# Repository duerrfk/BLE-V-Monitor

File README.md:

BLE-V-Monitor is a battery voltage monitor for vehicles (cars, motorbikes). It consists of an Arduino-based monitoring device and an Android app. The BLE-V-Monitor device is connected to the car battery to monitor the battery voltage and record voltage histories. The app queries the current voltage and voltage history via Bluetooth Low Energy (BLE) and displays them to the user.

The main features of BLE-V-Monitor are:

- Current voltage and battery charge status monitoring
- Recording of minutely, hourly, and daily voltage histories
- Bluetooth Low Energy (BLE) to transmit voltage samples to smartphones, tablets, Internet gateways, etc.
- Very low energy consumption
- Android app for displaying current voltage and voltage histories
- Open source hardware (CERN Open Hardware Licence v1.2) and software (Apache License 2.0)

The following images show the BLE-V-Monitor device and screenshots from the app.

# Implementation

BLE-V-Monitor consists of two parts: 

* the BLE-V-Monitor device (PCB and Arduino software)
* a smartphone app for Android. 

You can find the following files here:

* Schematics and PCB layout (Eagle files) of the monitoring device: directory `eagle`.
* Arduino source code for monitor device: directory `src`.
* BLE service definition for nRF8001 used by monitoring device: directory `nRFgo_studio`. 
* Android app source code: directory `android`.

The BLE-V-Monitor device periodically samples the voltage of the battery, and the app uses Bluetooth Low Energy (BLE) to query the battery voltage when the smartphone is close to the car. Instead of using a smartphone, you could also implement a client for other devices, e.g., a Raspberry Pi with a Bluetooth USB stick (not included so far).

## Prerequisites

To compile the code for the monitoring device, you need the Arduino IDE (tested with version 1.6.5).

Moreover, you need the Arduino BLE SDK from Nordic Semiconductors available 
from GitHub:

https://github.com/NordicSemiconductor/ble-sdk-arduino

1. Download SDK: `git clone https://github.com/NordicSemiconductor/ble-sdk-arduino.git`
2. Start the Arduino IDE (tested with v1.6.5)
3. Import the library: select `Sketch/Import library/Add` library and 
   then choose folder `libraries/BLE` from the downloaded SDK.
4. Check the availability of the library. There should be an entry `BLE`
   in menu `Sketch/Import library`.

The BLE services of nRF8001 are configured by the freely available nRFgo 
Studio tool (Windows application) [4]. This tool generates a file 
(`services.h`), which is also included in the repository. Thus, you  
only need to install this tool if you want to modify the BLE service 
description for some reason.

The Android app requires at least Android 4.3 (API level 18). You need to install Android Studio to edit the project provided in this repository.

## BLE-V-Monitor Device

The BLE-V-Monitor device is based on the Arduino platform. It uses an ATmega 328P microcontroller and the BLE module MOD-nRF8001 from Olimex [2] featuring a Nordic Semiconductor nRF8001 BLE chip [1]. The ATmega is programmed via an in-system programmer (ISP) and interfaces with the BLE module through SPI. Due to small duty cycles, the current consumption can be below 100 microampere while no client is connected via BLE.

To measure voltage, we use the 10 bit analog/digital converter (ADC) of the ATmega. The voltage range that can be measured ranges from 0 to 18 V, thus, the resolution is 18 V / 1024 = 17.6 mV. Note that while the car is running, the car's alternator provides more than 12 V to charge the battery (about 15 V for my car as can be seen from the history screenshot). A voltage divider with large resistor values (to save energy) is used to divide the battery voltage. Since we use 2.5 V reference voltage, 18 V is mapped to 2.5 V by the voltage divider. A precise 2.5 V reference voltage is provided by the micropower voltage reference diode LM285-2.5, which is only powered on demand through a GPIO pin of the ATmega during sampling. Since the resistors of the voltage divider have large values to save energy, a 100 nF capacitor in parallel to the second resistor of the voltage divider provides a low impedance source to the ADC (this 100 nF capacitor is much larger than the 14 pF sampling capacitor of the ATmega).  

A 18 V varistor protects from transient voltage spikes above 18 V. Since varistors typically age whenever they shunt excessive voltage, a (slow) fuse limits the current to protect against a short circuit of the varistor.

A micropower voltage regulator (LP295x) provides 3.3 V to the ATmega and BLE module. The 100 mA that can be provided by this regulator are more than sufficient to power the ATmega and BLE module while being active, and a very low quiescent current of only 75 microampere ensures efficient operation with small duty cycles.

## Programming the Monitoring Device

The monitoring device is programmed via ISP. The 6 pin ISP6 connector has the usual layout:

    MISO <-- 1 2 --> VCC
     SCK <-- 3 4 --> MOSI
     RST <-- 5 6 --> GND

You can leave the BLE module connected while programming the ATmega (the 
4.7 k resistors shield the SPI pins of the nRF8001 during programming). However,
you should use a 3.3 V programmer since the maximum voltage of the nRF8001
is 3.6 V.

To preprare the ATmega328P, program the following fuses (note that "0" means 
that the fuse is programmed):

* CKSEL = 0010: use internal 8 MHz RC oscillator
* CKDIV8 = 1: 8 MHz system clock (do not divide the 8 MHz internal clock by 8)
* SPIEN = 0: enable serial programming
* BODLEVEL = 101: brown-out detection set to 2.7 V
* SUT = 00: lowest possible startup time (6 CK from power-down; since we use
  BOD, we do not need additional waiting time for the power source to come up)
    
Using avrdude, the command looks like this (note: under Linux you might need
to execute this command as root depending on your programmer):

    $ avrdude -c usbasp -p m328p -U lfuse:w:0xc2:m -U hfuse:w:0xd9:m -U efuse:w:0x05:m

Make sure to compile your code for the correct board. In the repository, 
you will find a suitable board definition for the Arduino IDE (see folder 
`board_definition`). Copy the directory `ble-v-monitor` into the folder 
`hardware` in your Arduino sketchbook. Then you should find and select the 
board  called `BLE-V-Monitor -- ATmega328P @ 8 MHz` under the menu item `Tools/Board`. 

Compiling generates a hex file that we need to program the ATmega. This hex 
file is a little bit hidden in the temporary build directory of the Arduino
IDE. If you use Linux  and Arduino IDE 1.6, have a look at the `/tmp` 
directory. After hitting the  compile button in the Arduino IDE, search for the
latest hex file called  `ble-v-monitor.cpp.hex` in a temporary directory named 
`/tmp/build...`. If you have found the hex file, you can write it using avrdude
(again, you might need root right):

    $ avrdude -p m328p -c usbasp -v -U flash:w:/tmp/build6535101126624677692.tmp/ble-v-monitor.cpp.hex

## BLE-V-Monitor App

The BLE-V-Monitor App is implemented for Android 4.3 and above. It consists of a tab view with a fragment to display the current voltage, and three more fragments to display minutely, hourly, and daily voltage histories, respectively.

The charge status of a lead–acid car battery can be quite easily derived from its voltage. We use the following voltage levels to estimate the charge status: 

- 100 % charged (fully charged): about 12.66 V
- 75 % charged (charged): about 12.35 V
- 50 % charged (weakly charged): about 12.10 V
- 25 % charged (discharged): about 11.95 V
- 0 % charged (over discharged): about 11.7 V

# Licensing

BLE-V-Monitor uses two licenses for open hardware and software, respectively:

* The software (source code) is licensed under the Apache License 2.0 [5]
* The hardware (schematic diagrams, circuit board layouts, hardware
  documentation) is licensed under the CERN Open Hardware Licence v1.2 [6]

# References

* [1] https://www.nordicsemi.com/eng/Products/Bluetooth-Smart-Bluetooth-low-energy/nRF8001 
* [2] https://www.olimex.com/Products/Modules/RF/MOD-nRF8001/
* [3] https://github.com/NordicSemiconductor/ble-sdk-arduino
* [4] https://www.nordicsemi.com/chi/node_176/2.4GHz-RF/nRFgo-Studio
* [5] http://www.apache.org/licenses/LICENSE-2.0
* [6] http://www.ohwr.org/attachments/2388/cern_ohl_v_1_2.txt

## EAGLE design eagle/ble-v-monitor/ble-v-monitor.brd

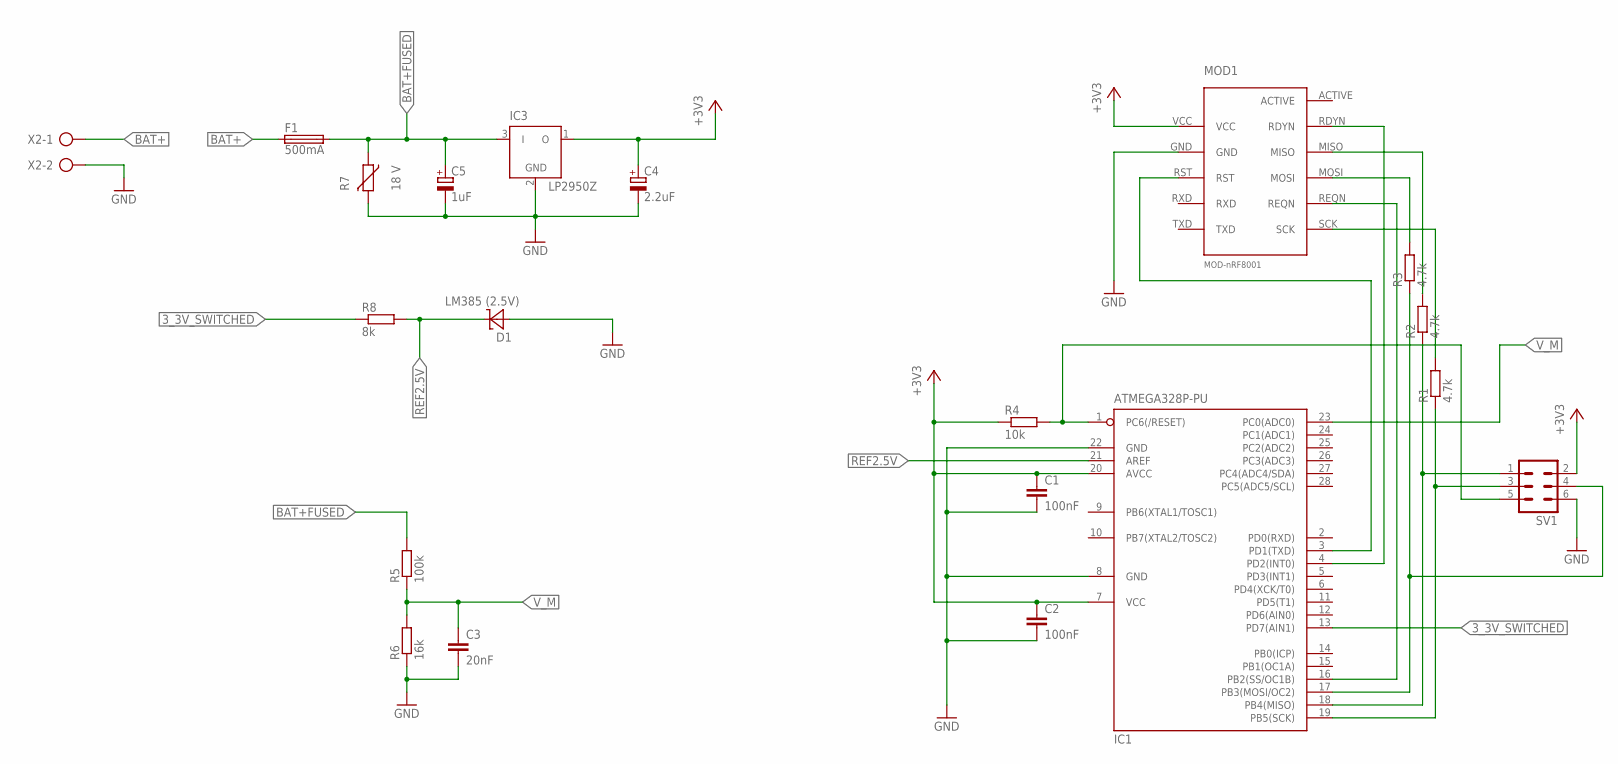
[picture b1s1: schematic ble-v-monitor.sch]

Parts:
C1, C2: 100nF; C050-024X044
C3: 20nF; C050-024X044
C4: 2.2uF; TT2D5
C5: 1uF; TT2D5
D1: LM385 (2.5V); TO-92
F1: 500mA; SH22,5
IC1: ATMEGA328P-PU; DIL28-3
IC3: LP2950Z; TO92
MOD1: MOD-NRF8001MOD-NRF8001; MOD-NRF8001
R1, R2, R3: 4.7k; 0207/7
R4: 10k; 0207/7
R5: 100k; 0207/7
R6: 16k; 0207/7
R7: 18 V; CT/CN0805
R8: 8k; 0207/7
SV1: MA03-2
X2: AK500/2

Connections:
3_3V_SWITCHED: IC1.13 (PD7(AIN1)), R8.1
+3V3: C1.1, C2.1, C4.+, IC1.7 (VCC), IC1.20 (AVCC), IC3.1 (O), MOD1.VCC, R4.1, SV1.2
BAT+: F1.1, X2.1
BAT+FUSED: C5.+, F1.2, IC3.3 (I), R5.2, R7.1
GND: C1.2, C2.2, C3.2, C4.-, C5.-, D1.+, IC1.8 (GND), IC1.22 (GND), IC3.2 (GND), MOD1.GND, R6.1, R7.2, SV1.6, X2.2
unnamed: MOD1.MOSI, R3.2
unnamed: IC1.1 (PC6(/RESET)), R4.2, SV1.5
unnamed: MOD1.SCK, R1.2
unnamed: IC1.19 (PB5(SCK)), R1.1, SV1.3
unnamed: MOD1.MISO, R2.2
unnamed: IC1.16 (PB2(SS/OC1B)), MOD1.REQN
unnamed: IC1.17 (PB3(MOSI/OC2)), R3.1, SV1.4
unnamed: IC1.3 (PD1(TXD)), MOD1.RST
unnamed: IC1.18 (PB4(MISO)), R2.1, SV1.1
unnamed: IC1.4 (PD2(INT0)), MOD1.RDYN
REF2.5V: D1.-, IC1.21 (AREF), R8.2
V_M: C3.1, IC1.23 (PC0(ADC0)), R5.1, R6.2

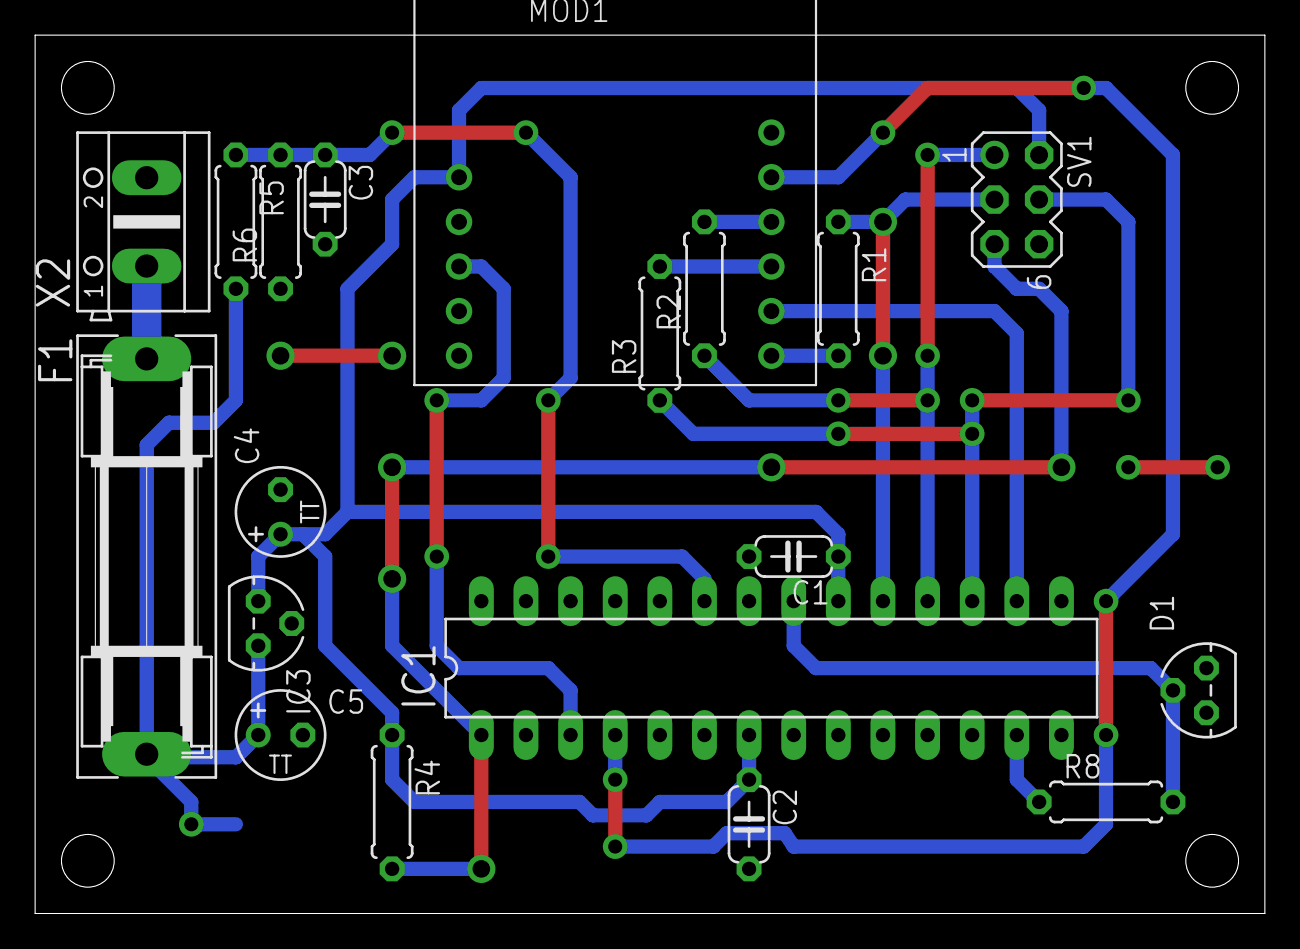
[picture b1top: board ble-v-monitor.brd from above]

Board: 2 copper layers, 70.0 x 50.0 mm, 20 parts (1 on the bottom side), 17 nets.

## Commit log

2016-01-01 Small modifications to readme
2016-05-05 Remove Eagle project file (not required)
